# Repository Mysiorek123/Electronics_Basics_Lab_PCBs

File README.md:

# Electronics_Basics_Lab_PCBs

[Common Emitter Documentation](https://github.com/Mysiorek123/Electronics_Basics_Lab_PCBs/blob/main/main/CE_TestBoard/Readme_CE.md)

[Operational Amplifier Documentation](https://github.com/Mysiorek123/Electronics_Basics_Lab_PCBs/blob/main/main/OpAmp_TestBoard/ReadmeOpAmp.md)

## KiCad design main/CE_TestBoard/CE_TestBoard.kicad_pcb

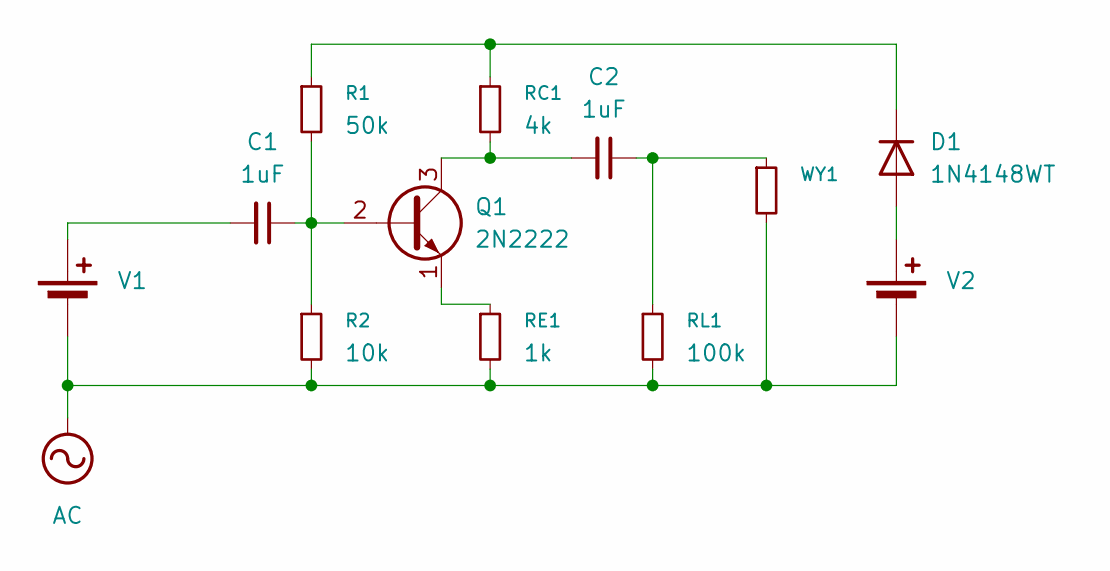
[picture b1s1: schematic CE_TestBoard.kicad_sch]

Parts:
C1, C2: 1uF; TerminalBlock_Phoenix_MKDS-1,5-2-5.08_1x02_P5.08mm_Horizont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
D1: 1N4148WT; D_5W_P12.70mm_Horizontal
Q1: 2N2222; TerminalBlock_Phoenix_MKDS-1,5-3-5.08_1x03_P5.08mm_Horizont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
R1: 50k; TerminalBlock_Phoenix_MKDS-1,5-2-5.08_1x02_P5.08mm_Horizont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
R2: 10k; TerminalBlock_Phoenix_MKDS-1,5-2-5.08_1x02_P5.08mm_Horizont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
RC1: 4k; TerminalBlock_Phoenix_MKDS-1,5-2-5.08_1x02_P5.08mm_Horizont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
RE1: 1k; TerminalBlock_Phoenix_MKDS-1,5-2-5.08_1x02_P5.08mm_Horizont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
RL1: 100k; TerminalBlock_Phoenix_MKDS-1,5-2-5.08_1x02_P5.08mm_Horizont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
V1, V2: TerminalBlock_Phoenix_MKDS-1,5-2-5.08_1x02_P5.08mm_Horizont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
WY1: TerminalBlock_Phoenix_MKDS-1,5-2-5.08_1x02_P5.08mm_Horizont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

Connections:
AC: R2.2, RE1.2, RL1.2, V1.2 (-), V2.2 (-), WY1.2
unnamed: C2.1, RL1.1, WY1.1
unnamed: D1.2 (A), V2.1 (+)
unnamed: D1.1 (K), R1.1, RC1.1
unnamed: C1.1, Q1.2 (B), R1.2, R2.1
unnamed: C2.2, Q1.3 (C), RC1.2
unnamed: Q1.1 (E), RE1.1
unnamed: C1.2, V1.1 (+)

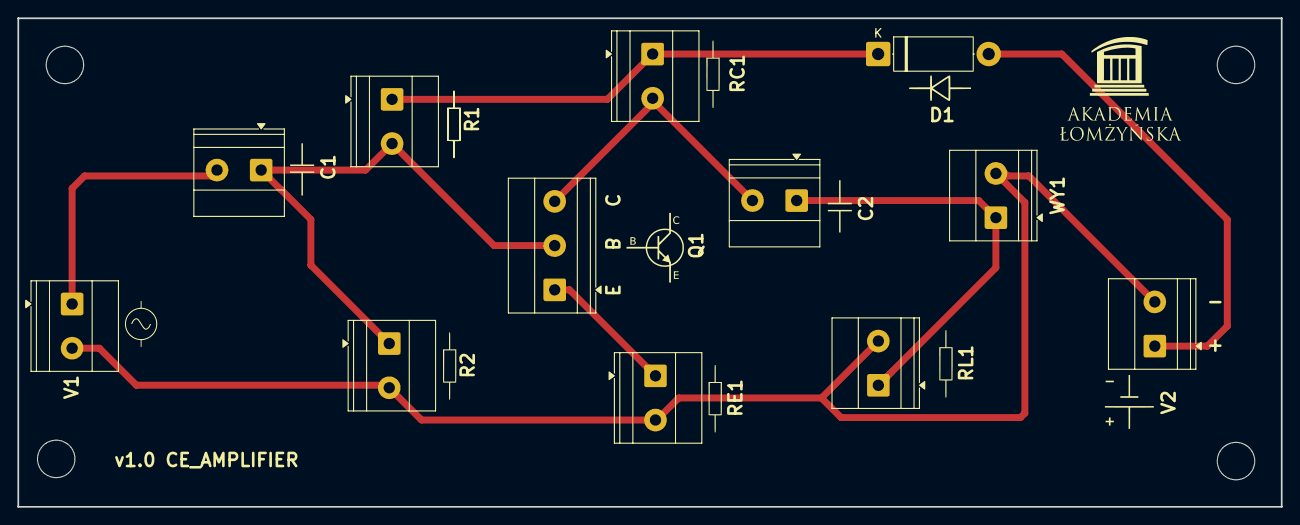
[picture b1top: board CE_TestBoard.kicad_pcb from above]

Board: 2 copper layers, 145.1 x 56.1 mm, 12 parts (0 on the bottom side), 8 nets.

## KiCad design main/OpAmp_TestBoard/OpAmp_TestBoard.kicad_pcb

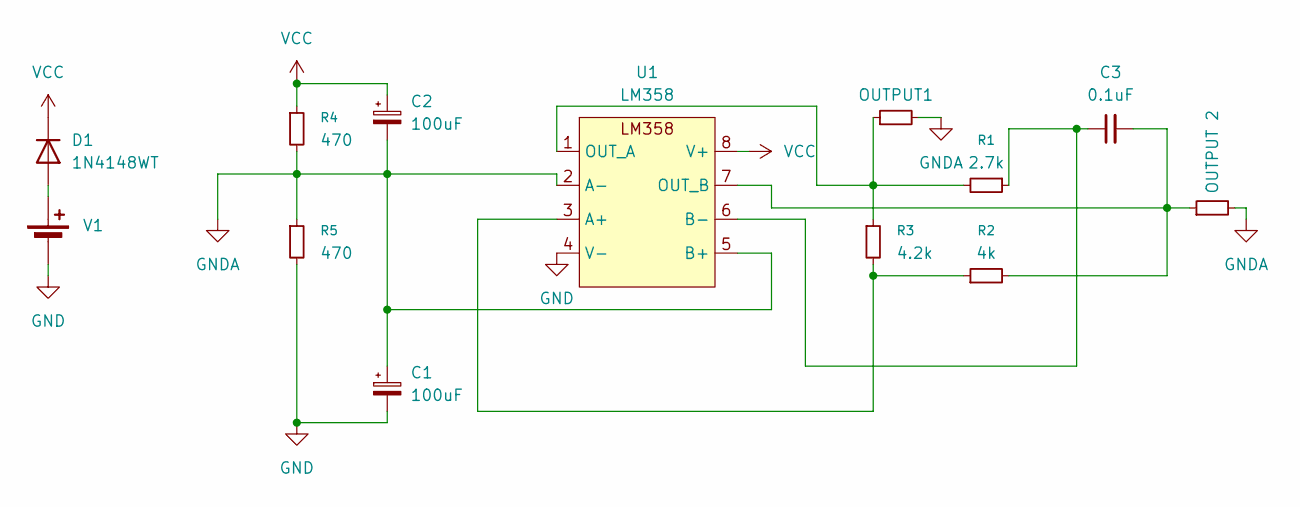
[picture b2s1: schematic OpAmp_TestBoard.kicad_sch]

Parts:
C1, C2: 100uF; TerminalBlock_Phoenix_MKDS-1,5-2-5.08_1x02_P5.08mm_Horizont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
C3: 0.1uF; TerminalBlock_Phoenix_MKDS-1,5-2-5.08_1x02_P5.08mm_Horizont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
D1: 1N4148WT; D_5W_P12.70mm_Horizontal
R1: 2.7k; TerminalBlock_Phoenix_MKDS-1,5-2-5.08_1x02_P5.08mm_Horizont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
R2: 4k; TerminalBlock_Phoenix_MKDS-1,5-2-5.08_1x02_P5.08mm_Horizont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
R3: 4.2k; TerminalBlock_Phoenix_MKDS-1,5-2-5.08_1x02_P5.08mm_Horizont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
R4, R5: 470; TerminalBlock_Phoenix_MKDS-1,5-2-5.08_1x02_P5.08mm_Horizont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
R6: OUTPUT 2; TerminalBlock_Phoenix_MKDS-1,5-2-5.08_1x02_P5.08mm_Horizont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
R7: OUTPUT1; TerminalBlock_Phoenix_MKDS-1,5-2-5.08_1x02_P5.08mm_Horizont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
U1: LM358; DIP-8_W7.62mm_Socket
V1: TerminalBlock_Phoenix_MKDS-1,5-2-5.08_1x02_P5.08mm_Horizont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

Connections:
GND: C1.2, R5.2, U1.4 (V-), V1.2 (-)
GNDA: C1.1, C2.2, R4.2, R5.1, R6.2, R7.2, U1.2 (A-), U1.5 (B+)
unnamed: D1.2 (A), V1.1 (+)
unnamed: R2.1, R3.2, U1.3 (A+)
unnamed: C3.1, R1.1, U1.6 (B-)
unnamed: R1.2, R3.1, R7.1, U1.1 (OUT_A)
unnamed: C3.2, R2.2, R6.1, U1.7 (OUT_B)
VCC: C2.1, D1.1 (K), R4.1, U1.8 (V+)

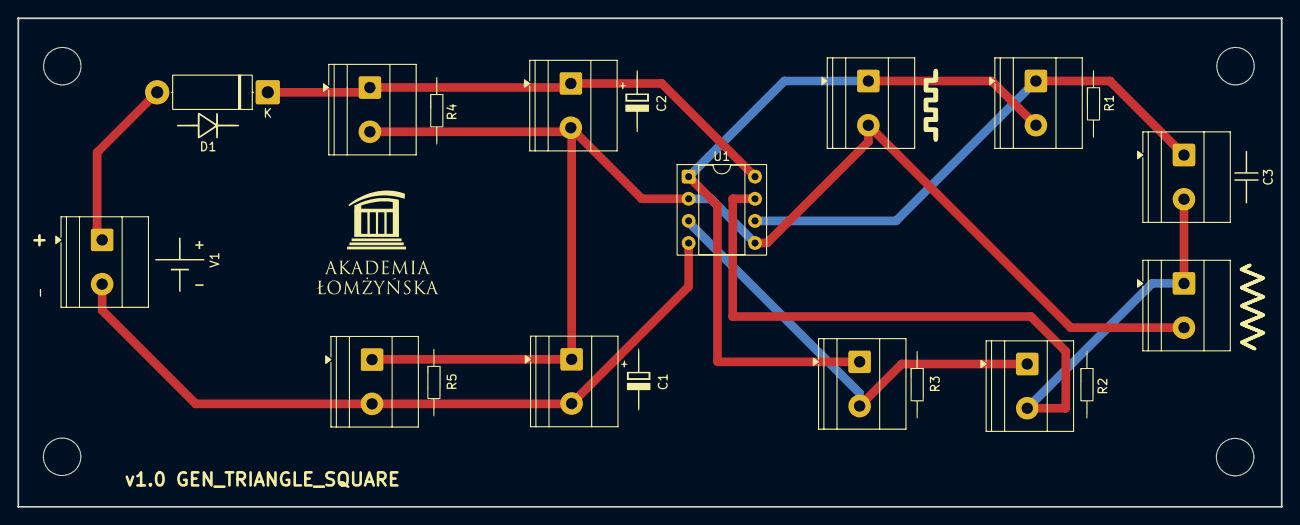
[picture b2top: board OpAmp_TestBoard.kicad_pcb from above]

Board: 2 copper layers, 145.1 x 56.1 mm, 14 parts (0 on the bottom side), 8 nets.

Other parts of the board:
C: LOGO; kondensator_bipolarny_symbol

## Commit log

2025-12-25 Uploaded first circuit boards and assets
2026-01-24 Repository has been reorganised + new safety changes and minor improvements
2026-01-29 Created new documents folder for Common Emitter Circuit
2026-01-29 Created README file for Common Emitter circuit
2026-01-29 Created new Documents folder for Operational Amplifier circuit
2026-01-29 Minor improvements
2026-01-29 Created README file for Operational Amplifier circuit
2026-01-29 Updated main README file.
2026-03-04 Minor fixes
2026-03-04 Edited Common Emitter README file
